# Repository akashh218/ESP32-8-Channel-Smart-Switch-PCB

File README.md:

# ESP32 8-Channel Smart Switch PCB

A custom **ESP32-based 8-channel smart switch PCB** designed in **KiCad**, focusing on relay interfacing, compact PCB layout, power distribution, grounding, and practical embedded hardware development.

## Overview

This project involves the design of an ESP32-based smart switching board, covering schematic design, component selection, PCB component placement, routing, and design-rule verification.

The board is designed to provide control of up to eight switching channels, enabling multiple electrical loads to be controlled through an ESP32-based system.

## Key Features

- ESP32-based control architecture
- 8-channel relay switching interface
- Multi-load switching capability
- Wireless control capability through ESP32 connectivity
- Dedicated power distribution for the control circuitry
- Ground plane and grounding optimization
- PCB component placement and routing
- Design-rule checking (DRC)
- Compact PCB layout for automation applications

## PCB Design Approach

The PCB design focuses on:

- Component placement and functional grouping
- ESP32 pin assignment and signal routing
- Relay control signal routing
- Power supply distribution
- Grounding and return-current paths
- Decoupling capacitor placement
- Trace width selection based on current requirements
- Clearance between control circuitry and switched-load connections
- Manufacturing clearances and footprint verification
- PCB design-rule checking

GPIO assignments and component placement were planned to simplify routing and improve the overall organization of the board.

## Design Challenges

Some of the main design considerations include:

- Routing eight independent relay control signals
- Managing power distribution across multiple switching channels
- Optimizing ESP32 placement and GPIO connectivity
- Maintaining suitable trace widths and clearances
- Organizing relay connectors for convenient wiring
- Balancing PCB size with component accessibility
- Resolving design-rule and footprint issues

## Tools

- **KiCad** – Schematic capture and PCB layout
- **KiCad DRC** – Design-rule verification

## Repository Contents

This repository contains the design files associated with the project, including:

- Schematic files
- PCB layout files
- Footprints and libraries used by the design
- Design documentation
- Gerber files and manufacturing outputs, if included

## Project Status

**PCB Design in Progress / Completed**

The project status will be updated as the design progresses through PCB fabrication, component assembly, power-up verification, relay switching tests, and functional validation.

## Learning Outcomes

This project focuses on developing practical skills in:

- PCB schematic design and layout
- ESP32 hardware integration
- Relay interfacing
- Power distribution and grounding
- GPIO planning and signal routing
- Component and footprint selection
- PCB design-rule verification
- Hardware debugging and testing
- Design for manufacturability

---

**Designed in KiCad | ESP32 | 8-Channel Smart Switch PCB**

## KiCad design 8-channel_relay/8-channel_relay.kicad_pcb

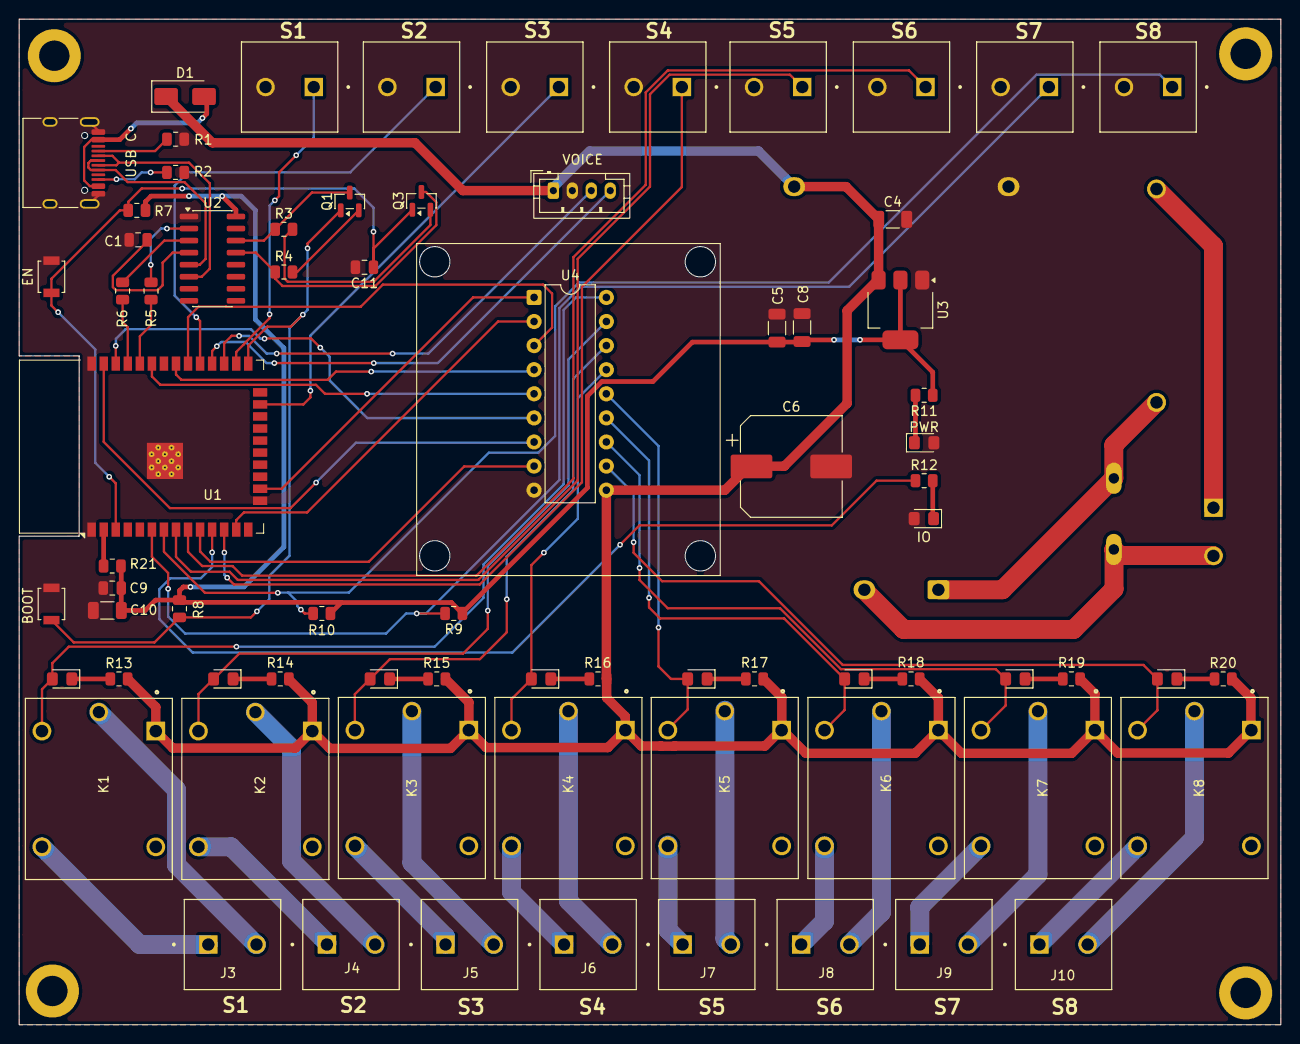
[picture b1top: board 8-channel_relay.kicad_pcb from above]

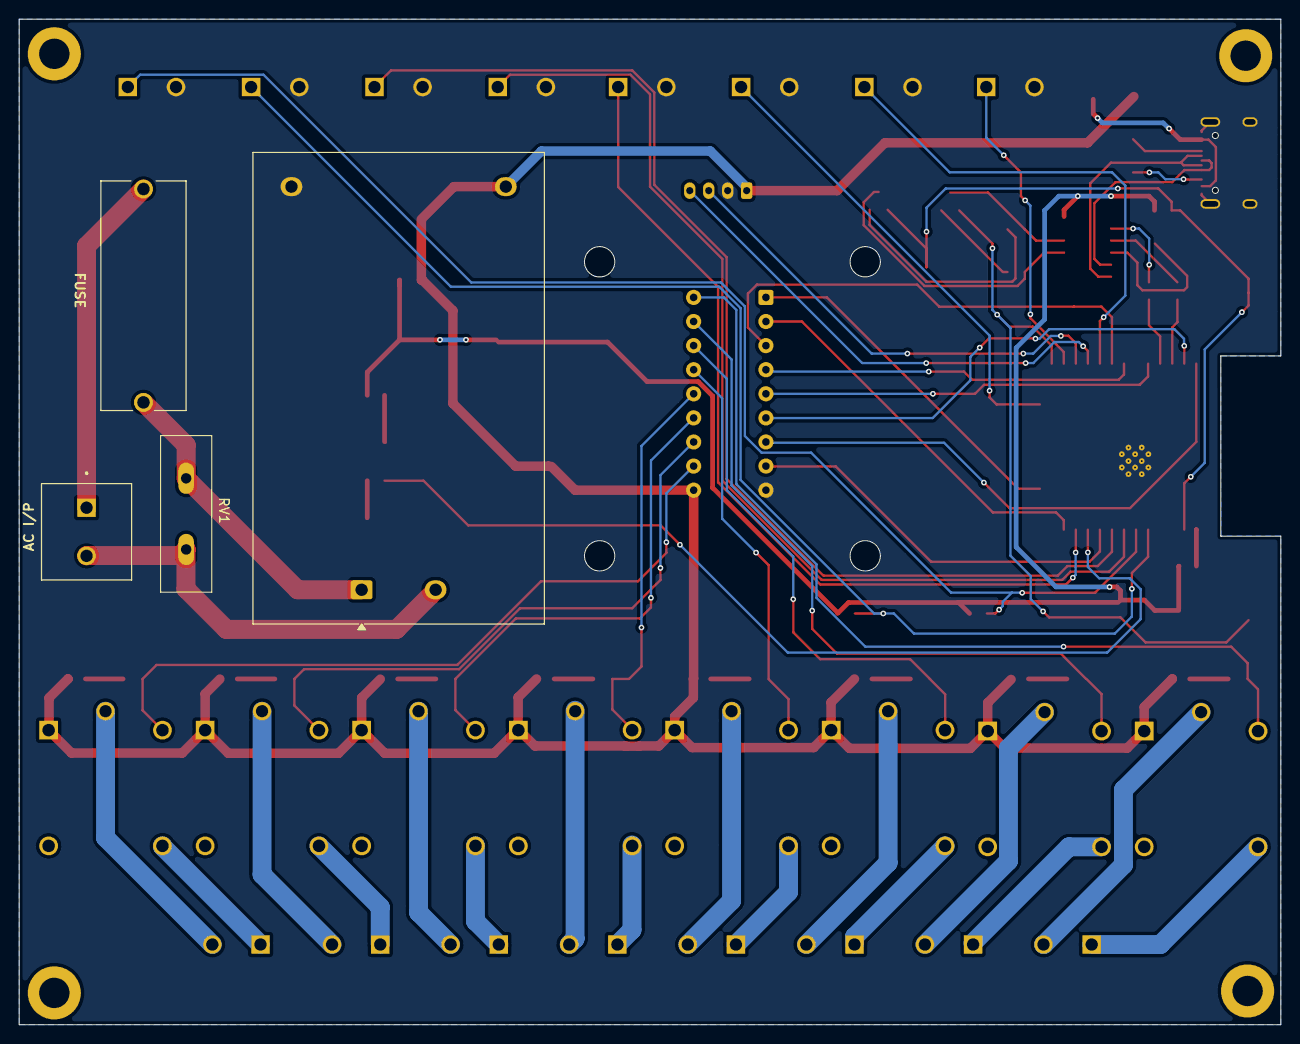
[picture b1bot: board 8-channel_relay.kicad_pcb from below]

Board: 2 copper layers, 133.0 x 106.0 mm, 78 parts (4 on the bottom side), 76 nets.

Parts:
AC I/P: I/P AC; PHOENIX_1888687
BOOT: SW_Push; SW_SPST_B3U-1000P
C1: 100nF; C_0805_2012Metric
C4, C5, C10: 10µF; C_1206_3216Metric
C6: 470µF; CP_Elec_10x10.5
C8: 0.1µF; C_1206_3216Metric
C9, C11: 0.1µF; C_0805_2012Metric
D1: D_Schottky; D_SMA
D5, D6, D7, D8, D9, D10, D11, D12: LED; LED_0805_2012Metric_Pad1.15x1.40mm_HandSolder
EN: SW_Push; SW_SPST_B3U-1000P
FUSE: 4628; FUSE_4628
IO: LED; LED_0805_2012Metric_Pad1.15x1.40mm_HandSolder
J3: S1; PHOENIX_1888687
J4: S2; PHOENIX_1888687
J5: S3; PHOENIX_1888687
J6: S4; PHOENIX_1888687
J7: S5; PHOENIX_1888687
J8: S6; PHOENIX_1888687
J9: S7; PHOENIX_1888687
J10: S8; PHOENIX_1888687
J12: ES1; PHOENIX_1888687
J13: ES2; PHOENIX_1888687
J14: ES3; PHOENIX_1888687
J15: ES4; PHOENIX_1888687
J16: ES5; PHOENIX_1888687
J17: ES6; PHOENIX_1888687
J18: ES7; PHOENIX_1888687
J19: ES8; PHOENIX_1888687
K1, K2, K3, K4, K5, K6, K7, K8: SRD-05VDC-SL-C; RELAY_SRD-05VDC-SL-C
PWR: PWR; LED_0805_2012Metric_Pad1.15x1.40mm_HandSolder
Q1, Q3: NPN; SOT-23
R1, R2: 5.1K; R_0805_2012Metric
R3, R4, R7, R8, R9, R10: 10K; R_0805_2012Metric
R5, R6: 470Ω; R_0805_2012Metric
R11, R12: 330Ω; R_0805_2012Metric
R13, R14, R15, R16, R17, R18, R19, R20: 1k; R_0805_2012Metric
R21: 0E; R_0805_2012Metric
RV1: MOV-14D471K; MOV14D471K
U1: ESP32-WROOM-32D
U2: CH340C; SOIC-16_3.9x9.9mm_P1.27mm
U3: AMS1117-3.3; SOT-223-3_TabPin2
U4: ULN2803A; DIP-18_W7.62mm
U5: HLK-10M05; Converter_ACDC_Hi-Link_HLK-10Mxx
USB C: USB_C_Receptacle_USB2.0_16P; USB_C_Receptacle_HRO_TYPE-C-31-M-12
VOICE: VOICE; JST_PH_B4B-PH-K_1x04_P2.00mm_Vertical

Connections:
+3.3V: C5.1, C8.1, C9.2, C10.1, R7.1, R8.1, R9.1, R10.1, R11.1, R21.1, U2.16 (VCC), U3.2 (VO)
+5V: C4.1, C6.1, D1.1 (K), K1.A1, K2.A1, K3.A1, K4.A1, K5.A1, K6.A1, K7.A1, K8.A1, R13.1, R14.1, R15.1, R16.1, R17.1, R18.1, R19.1, R20.1, U3.3 (VI), U4.10 (COM), U5.4 (+Vout), VOICE.1
/ESP/BOOT: BOOT.1, Q1.1 (C), R8.2, U1.25 (IO0)
/ESP/DTR: Q3.3 (E), R4.1, U2.13 (~DTR)
/ESP/EN: C11.1, EN.1, Q3.1 (C), R7.2, U1.3 (EN)
/ESP/IO LED: R12.1, U1.11 (IO26)
/ESP/RTS: Q1.3 (E), R3.1, U2.14 (~RTS)
/ESP/SCL: U1.28 (IO17), VOICE.4
/ESP/SDA: U1.27 (IO16), VOICE.3
/ESP/UD+: U2.5 (UD+), USB C.A6 (D+), USB C.B6 (D+)
/ESP/UD-: U2.6 (UD-), USB C.A7 (D-), USB C.B7 (D-)
/ESP/URX: R5.2, U1.34 (RXD0/IO3)
/ESP/UTX: R6.2, U1.35 (TXD0/IO1)
/POWER+RELAY/COM1: J3.2, K1.COM
/POWER+RELAY/COM2: J4.2, K2.COM
/POWER+RELAY/COM3: J5.2, K3.COM
/POWER+RELAY/COM4: J6.2, K4.COM
/POWER+RELAY/COM5: J7.2, K5.COM
/POWER+RELAY/COM6: J8.2, K6.COM
/POWER+RELAY/COM7: J9.2, K7.COM
/POWER+RELAY/COM8: J10.2, K8.COM
/POWER+RELAY/NO1: J3.1, K1.NO
/POWER+RELAY/NO2: J4.1, K2.NO
/POWER+RELAY/NO3: J5.1, K3.NO
/POWER+RELAY/NO4: J6.1, K4.NO
/POWER+RELAY/NO5: J7.1, K5.NO
/POWER+RELAY/NO6: J8.1, K6.NO
/POWER+RELAY/NO7: J9.1, K7.NO
/POWER+RELAY/NO8: J10.1, K8.NO
/POWER+RELAY/OUT1: D5.2 (A), K1.A2, U4.18 (O1)
/POWER+RELAY/OUT2: D6.2 (A), K2.A2, U4.17 (O2)
/POWER+RELAY/OUT3: D7.2 (A), K3.A2, U4.16 (O3)
/POWER+RELAY/OUT4: D8.2 (A), K4.A2, U4.15 (O4)
/POWER+RELAY/OUT5: D9.2 (A), K5.A2, U4.14 (O5)
/POWER+RELAY/OUT6: D10.2 (A), K6.A2, U4.13 (O6)
/POWER+RELAY/OUT7: D11.2 (A), K7.A2, U4.12 (O7)
/POWER+RELAY/OUT8: D12.2 (A), K8.A2, U4.11 (O8)
ES1: J12.1, U1.26 (IO4)
ES2: J13.1, U1.29 (IO5)
ES3: J14.1, U1.23 (IO15)
ES4: J15.1, U1.12 (IO27)
ES5: J16.1, U1.8 (IO32)
ES6: J17.1, U1.9 (IO33)
ES7: J18.1, R9.2, U1.6 (IO34)
ES8: J19.1, R10.2, U1.7 (IO35)
GND: BOOT.2, C1.2, C4.2, C5.2, C6.2, C8.2, C9.1, C10.2, C11.2, EN.2, IO.2 (A), J12.2, J13.2, J14.2, J15.2, J16.2, J17.2, J18.2, J19.2, PWR.2 (A), R1.2, R2.2, U1.1 (GND), U1.15 (GND), U1.38 (GND), U1.39 (GND), U2.1 (GND), U3.1 (GND), U4.9 (GND), U5.3 (-Vout), USB C.A1 (GND), USB C.A12 (GND), USB C.B1 (GND), USB C.B12 (GND), USB C.SH (SHIELD), VOICE.2
unnamed: D1.2 (A), USB C.A4 (VBUS), USB C.A9 (VBUS), USB C.B4 (VBUS), USB C.B9 (VBUS)
unnamed: PWR.1 (K), R11.2
unnamed: IO.1 (K), R12.2
unnamed: D5.1 (K), R13.2
unnamed: D6.1 (K), R14.2
unnamed: D7.1 (K), R15.2
unnamed: D8.1 (K), R16.2
unnamed: D9.1 (K), R17.2
unnamed: D10.1 (K), R18.2
unnamed: D11.1 (K), R19.2
unnamed: D12.1 (K), R20.2
unnamed: R1.1, USB C.A5 (CC1)
unnamed: R2.1, USB C.B5 (CC2)
unnamed: AC I/P.1, FUSE.1
unnamed: AC I/P.2, RV1.2, U5.2 (AC/N)
unnamed: Q1.2 (B), R4.2
unnamed: Q3.2 (B), R3.2
unnamed: R21.2, U1.2 (VDD)
unnamed: R6.1, U2.3 (RXD)
unnamed: R5.1, U2.2 (TXD)
unnamed: C1.1, U2.4 (V3)
unnamed: FUSE.2, RV1.1, U5.1 (AC/L)
S1: U1.16 (IO13), U4.1 (I1)
S2: U1.13 (IO14), U4.2 (I2)
S3: U1.30 (IO18), U4.3 (I3)
S4: U1.31 (IO19), U4.4 (I4)
S5: U1.33 (IO21), U4.5 (I5)
S6: U1.36 (IO22), U4.6 (I6)
S7: U1.37 (IO23), U4.7 (I7)
S8: U1.10 (IO25), U4.8 (I8)
